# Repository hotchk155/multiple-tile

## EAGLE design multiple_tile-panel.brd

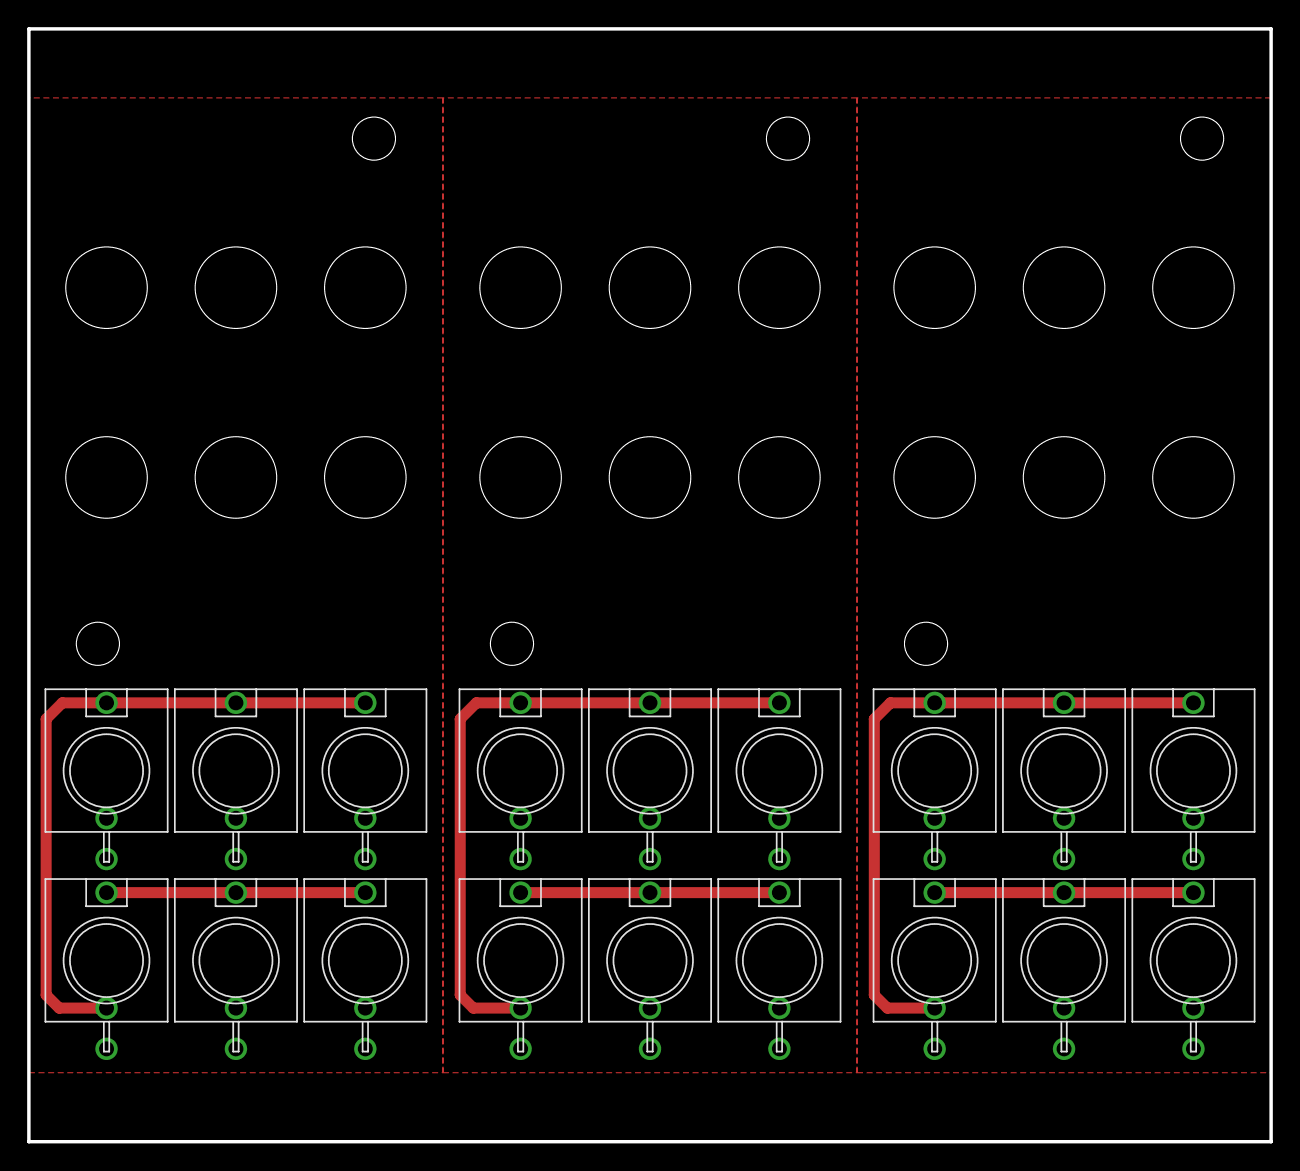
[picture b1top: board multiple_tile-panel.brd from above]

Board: 2 copper layers, 91.4 x 81.9 mm, 18 parts (0 on the bottom side), 9 nets.

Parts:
U$1, U$2, U$3, U$4, U$5, U$6, U$7, U$8, U$9, U$10, U$11, U$12, U$13, U$14, U$15, U$16, U$17, U$18: WQP-PJ301M-12_JACK

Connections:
GND: U$1.P$3, U$2.P$3, U$3.P$3, U$4.P$3, U$5.P$3, U$6.P$3
GND1: U$7.P$3, U$8.P$3, U$9.P$3, U$10.P$3, U$11.P$3, U$12.P$3
GND2: U$13.P$3, U$14.P$3, U$15.P$3, U$16.P$3, U$17.P$3, U$18.P$3
SIG1: U$1.P$1, U$2.P$1, U$3.P$1, U$6.P$2
SIG2: U$4.P$1, U$5.P$1, U$6.P$1
SIG3: U$10.P$1, U$11.P$1, U$12.P$1
SIG4: U$7.P$1, U$8.P$1, U$9.P$1, U$12.P$2
SIG5: U$16.P$1, U$17.P$1, U$18.P$1
SIG6: U$13.P$1, U$14.P$1, U$15.P$1, U$18.P$2

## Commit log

2018-12-03 repanelize - v3
2021-05-10 saas
